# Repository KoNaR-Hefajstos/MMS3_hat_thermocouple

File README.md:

Dokumentacja Hat'a: Moduł wejść termopar

## Sekcja 1: Dokumentacja Hat'a

### Krótki opis projektu
Hat thermoucople umożliwia wykonywanie pomiarów temperatury przy użyciu termopar. 
Płytka jest wyposażona w 8 wejść oraz przetwornik analogowy cyfrowy, dedykowany do obsługi termopar typu K ze zintegrowaną kompensacją zimnego końca

### Zgodność ze standardem ChainBus

* ✅  Używa złącza ChainBus, nie zmienia jego miejsca ani pinoutu.
* ✅  Używa wyłącznie interfejsów I2C, SPI lub UART i nie inicjuje samodzielnie nowych transmisji (Nie jest master'em I2C albo SPI).
* ✅  Spełnia wymagania mechaniczne standardu (wymiary PCB, rozstaw otworów).
* ✅  Pobiera maksymalny prąd zgodny z ilością na jednego hat'a
* ✅  Obsługuje napięcie wejściowe BRD_VIN do wartości 48V.

### Komunikacja i adresowanie
Układ komunikuje się za pomocą jednokierunkowego interfejsu SPI w trybie tylko do odczytu. 
To które wyjście jest aktualnie odczytywane zależy od stanu pinu CS układu scalonego MAX31855KASA+T, do ustalaniu stanu tych pinów zastosowany został I2C multipexer

| Układ (IC)                | Funkcja         |  Address   |
| :------------             | :-------------- | :--------: |
| **TCA9535PWR_C130204**    | I2C multiplexer | `0000000b` |

#### Magistrala SPI
Urządzenia SPI podłączone są bezpośrednio do magistrali systemowej bez użycia dodatkowych multiplekserów.

| Układ (IC)         | Funkcja                     | chainbus/multiplexer |
| :----------        | :-------------------------- | :------------------: |
| **MAX31855KASA+T** | Sterownik silnika krokowego |      `chainbus`      |

### Pinout złączy

| Jn       | Co              | Jaki pin co robi                                                       |
| :-----   | :---------------| :----------------------------------------------------------------------|
| **TH00** | Termopara 1     | Pin 1 Ujemne wejście Termopary<br> Pin 2 Dodatnie wejście Termopary<br>|
| **TH01** | Termopara 2     | Pin 1 Ujemne wejście Termopary<br> Pin 2 Dodatnie wejście Termopary<br>|
| **TH02** | Termopara 3     | Pin 1 Ujemne wejście Termopary<br> Pin 2 Dodatnie wejście Termopary<br>|
| **TH03** | Termopara 4     | Pin 1 Ujemne wejście Termopary<br> Pin 2 Dodatnie wejście Termopary<br>|
| **TH04** | Termopara 5     | Pin 1 Ujemne wejście Termopary<br> Pin 2 Dodatnie wejście Termopary<br>|
| **TH05** | Termopara 6     | Pin 1 Ujemne wejście Termopary<br> Pin 2 Dodatnie wejście Termopary<br>|
| **TH06** | Termopara 7     | Pin 1 Ujemne wejście Termopary<br> Pin 2 Dodatnie wejście Termopary<br>|
| **TH07** | Termopara 8     | Pin 1 Ujemne wejście Termopary<br> Pin 2 Dodatnie wejście Termopary<br>|

### Typ możliwych termopar 
Termopary typu K, J, N, T, S, R lub E. Przetwornik umożliwia rozdzielczość temperatury do 0,25°C, pozwala na odczyty do +1800°C i tak niskie jak -270°C, a dokładność termopary wynosi ±2°C dla temperatur od -200°C do +700°C w przypadku termopar typu K.

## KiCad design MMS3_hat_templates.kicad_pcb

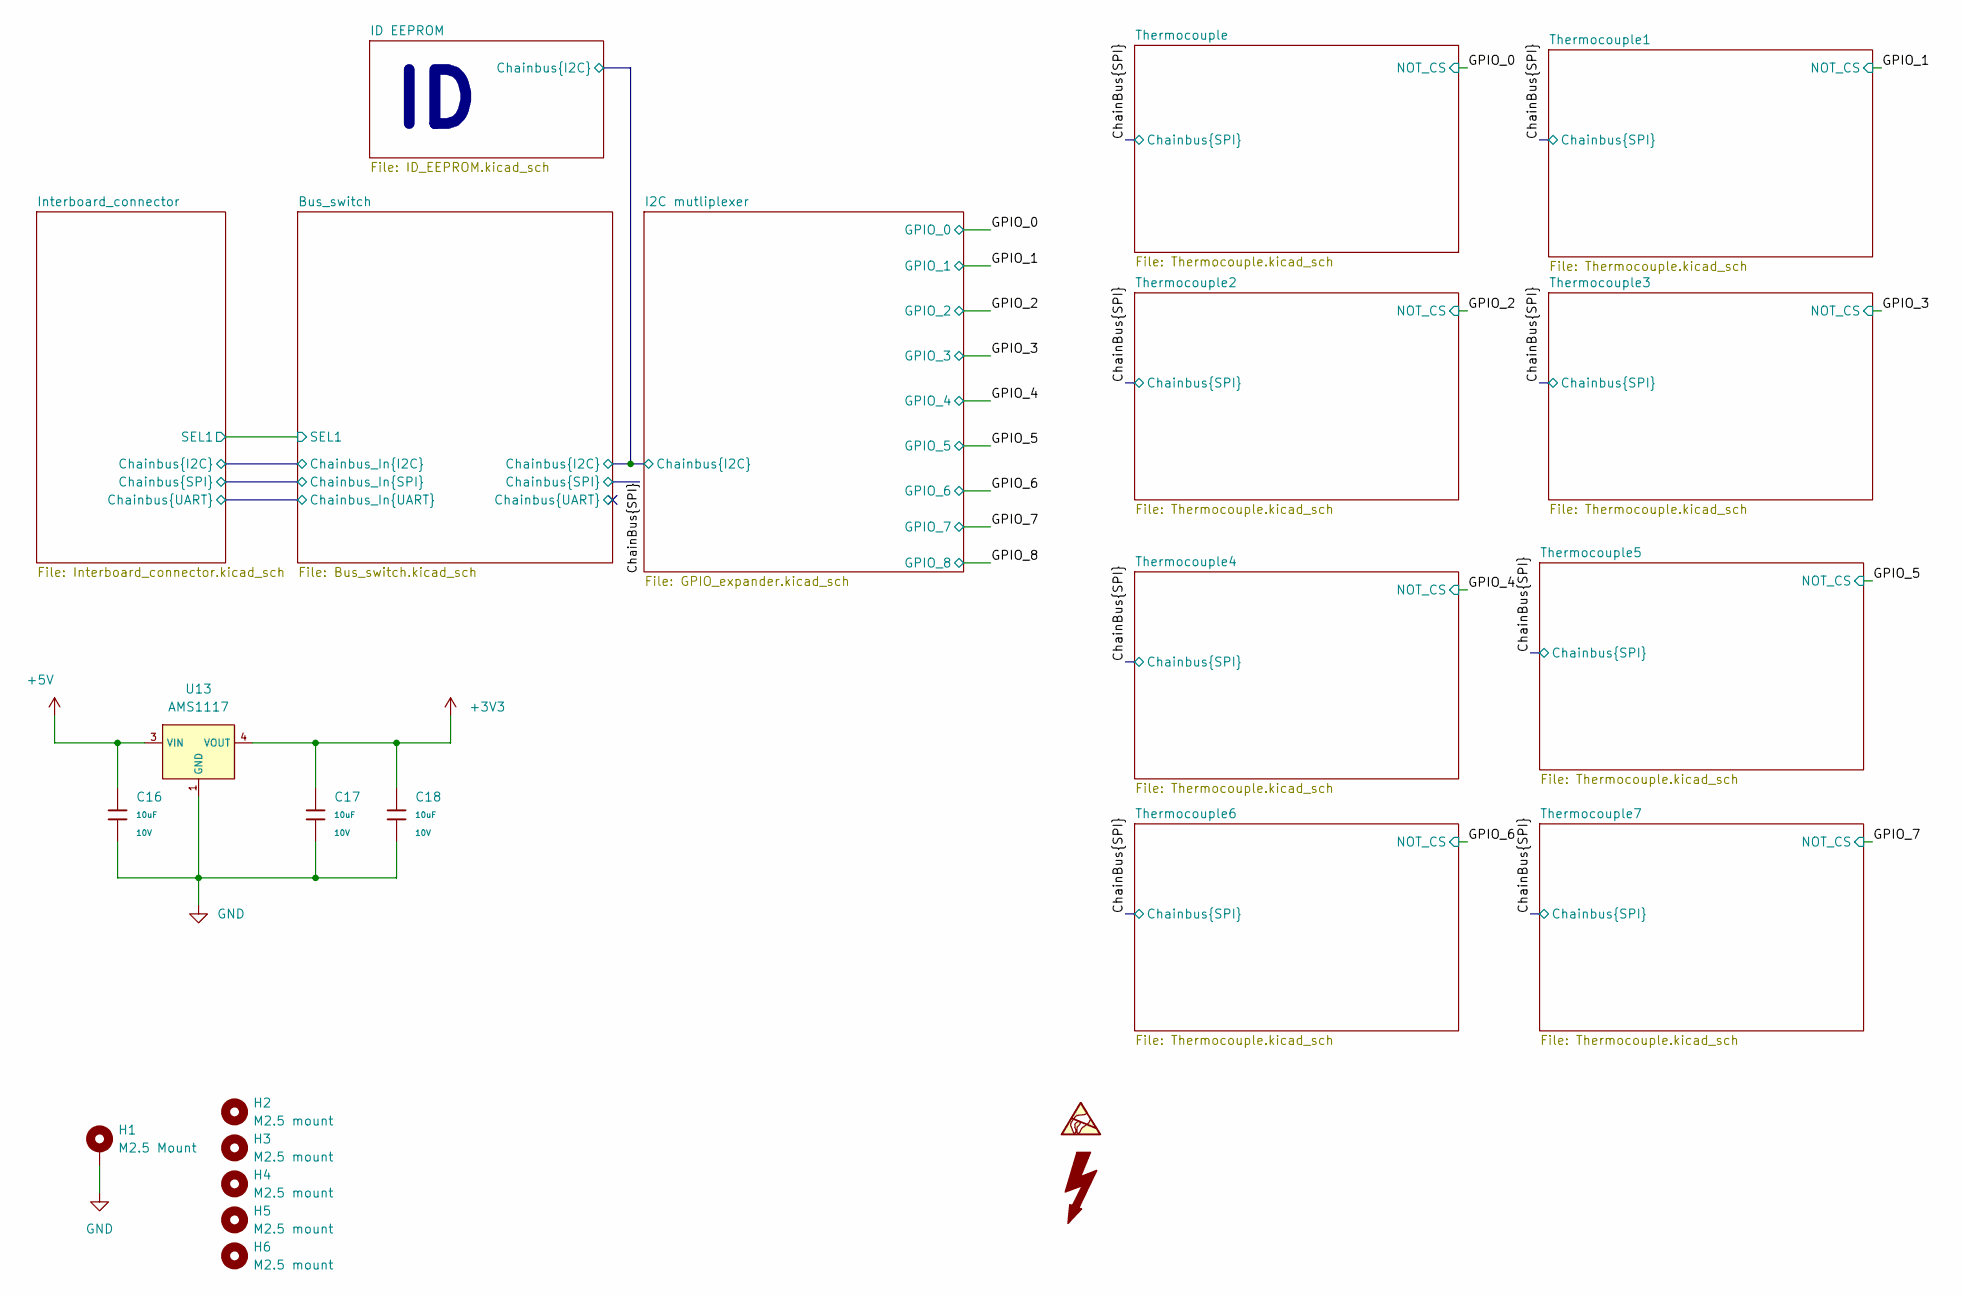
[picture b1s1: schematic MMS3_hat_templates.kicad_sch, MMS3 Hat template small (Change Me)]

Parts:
C16, C17, C18: 10uF; C_0603; Voltage Rated 10V; Tolerance ±10%; Part CL10A106KP8NNNC; LCSC C19702
H1: M2.5 Mount; MountingHole_2.7mm_M2.5_DIN965_Pad_TopOnly
H2, H3, H4, H5, H6: M2.5 mount; MountingHole_2.7mm_M2.5
U13: AMS1117; SOT-223-3_L6.5-W3.4-P2.30-LS7.0-BR; Output Voltage 3.3V; Dropout Voltage 1.3V@(800mA); Part AMS1117-3.3; LCSC C6186

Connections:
+3V3: C17.1, C18.1, U13.2 (VOUT), U13.4 (VOUT); also elsewhere on the board
+5V: C16.1, U13.3 (VIN); also elsewhere on the board
GND: C16.2, C17.2, C18.2, H1.1 (1_1), U13.1 (GND); also elsewhere on the board

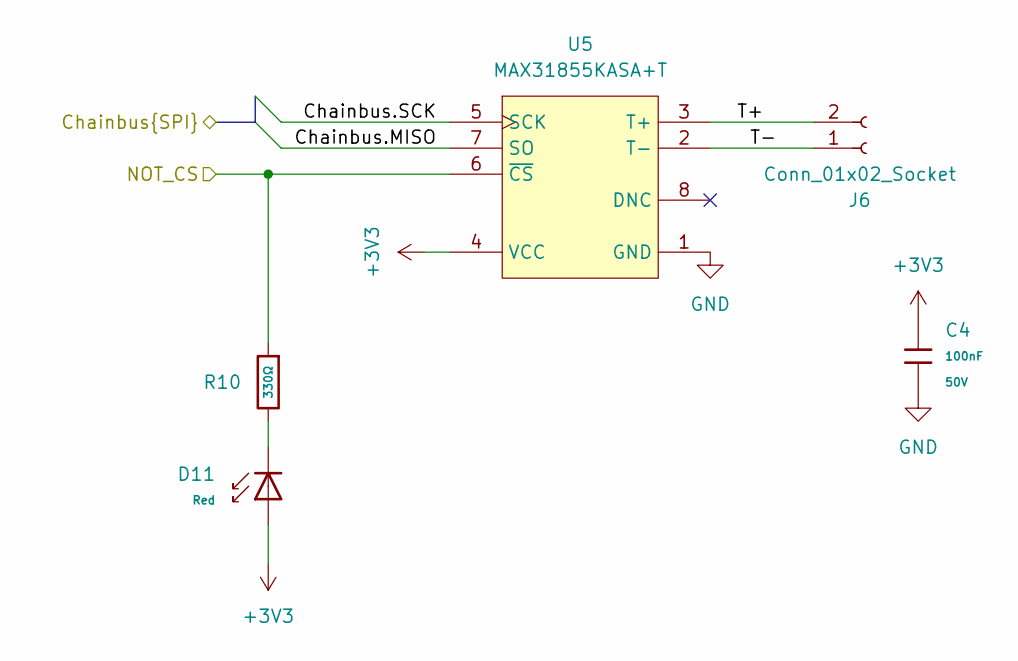
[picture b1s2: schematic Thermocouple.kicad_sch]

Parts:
C4: 100nF; C_0603; Voltage Rated 50V; Tolerance ±10%; Part CC0603KRX7R9BB104; LCSC C14663
D11: Red; D_0603; Part KT-0603R; LCSC C2286
J6: Conn_01x02_Socket; JST_XH_S2B-XH-A_1x02_P2.50mm_Horizontal
R10: 330Ω; R_0402; Overload Voltage (Max) 50V; Tolerance ±1%; Part 0402WGF3300TCE; LCSC C25104
U5: MAX31855KASA+T; SO-8_L4.9-W3.9-P1.27-LS5.9-BL; MPN MAX31855KASA+T; LCSC Part C52028

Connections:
+3V3: C4.1, D11.2, U5.4 (VCC); also elsewhere on the board
/ChainBus.MISO: U5.7 (SO); also elsewhere on the board
/ChainBus.SCK: U5.5 (SCK); also elsewhere on the board
/GPIO_1: R10.1, U5.6 (~CS); also elsewhere on the board
/Thermocouple1/T+: J6.2, U5.3 (T+)
/Thermocouple1/T-: J6.1, U5.2 (T-)
GND: C4.2, U5.1 (GND); also elsewhere on the board
unnamed: D11.1, R10.2

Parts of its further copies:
C5, C6, C7, C8, C9, C10, C11: 100nF; C_0603; Voltage Rated 50V; Tolerance ±10%; Part CC0603KRX7R9BB104; LCSC C14663
D12, D13, D14, D15, D16, D17, D18: Red; D_0603; Part KT-0603R; LCSC C2286
J7, J8, J9, J10, J11, J12, J13: Conn_01x02_Socket; JST_XH_S2B-XH-A_1x02_P2.50mm_Horizontal
R11, R12, R13, R14, R15, R16, R17: 330Ω; R_0402; Overload Voltage (Max) 50V; Tolerance ±1%; Part 0402WGF3300TCE; LCSC C25104
U16, U17, U18, U19, U20, U21, U22: MAX31855KASA+T; SO-8_L4.9-W3.9-P1.27-LS5.9-BL; MPN MAX31855KASA+T; LCSC Part C52028

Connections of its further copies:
+3V3: C5.1, C6.1, C7.1, C8.1, C9.1, C10.1, C11.1, D12.2, D13.2, D14.2, D15.2, D16.2, D17.2, D18.2, U16.4 (VCC), U17.4 (VCC), U18.4 (VCC), U19.4 (VCC), U20.4 (VCC), U21.4 (VCC), U22.4 (VCC); also elsewhere on the board
/ChainBus.MISO: U16.7 (SO), U17.7 (SO), U18.7 (SO), U19.7 (SO), U20.7 (SO), U21.7 (SO), U22.7 (SO); also elsewhere on the board
/ChainBus.SCK: U16.5 (SCK), U17.5 (SCK), U18.5 (SCK), U19.5 (SCK), U20.5 (SCK), U21.5 (SCK), U22.5 (SCK); also elsewhere on the board
/GPIO_0: R11.1, U16.6 (~CS); also elsewhere on the board
/GPIO_2: R12.1, U17.6 (~CS); also elsewhere on the board
/GPIO_3: R13.1, U18.6 (~CS); also elsewhere on the board
/GPIO_4: R14.1, U19.6 (~CS); also elsewhere on the board
/GPIO_5: R15.1, U20.6 (~CS); also elsewhere on the board
/GPIO_6: R16.1, U21.6 (~CS); also elsewhere on the board
/GPIO_7: R17.1, U22.6 (~CS); also elsewhere on the board
/Thermocouple2/T+: J8.2, U17.3 (T+)
/Thermocouple2/T-: J8.1, U17.2 (T-)
/Thermocouple3/T+: J9.2, U18.3 (T+)
/Thermocouple3/T-: J9.1, U18.2 (T-)
/Thermocouple4/T+: J10.2, U19.3 (T+)
/Thermocouple4/T-: J10.1, U19.2 (T-)
/Thermocouple5/T+: J11.2, U20.3 (T+)
/Thermocouple5/T-: J11.1, U20.2 (T-)
/Thermocouple6/T+: J12.2, U21.3 (T+)
/Thermocouple6/T-: J12.1, U21.2 (T-)
/Thermocouple7/T+: J13.2, U22.3 (T+)
/Thermocouple7/T-: J13.1, U22.2 (T-)
/Thermocouple/T+: J7.2, U16.3 (T+)
/Thermocouple/T-: J7.1, U16.2 (T-)
GND: C5.2, C6.2, C7.2, C8.2, C9.2, C10.2, C11.2, U16.1 (GND), U17.1 (GND), U18.1 (GND), U19.1 (GND), U20.1 (GND), U21.1 (GND), U22.1 (GND); also elsewhere on the board
unnamed: D12.1, R11.2
unnamed: D13.1, R12.2
unnamed: D14.1, R13.2
unnamed: D15.1, R14.2
unnamed: D16.1, R15.2
unnamed: D17.1, R16.2
unnamed: D18.1, R17.2

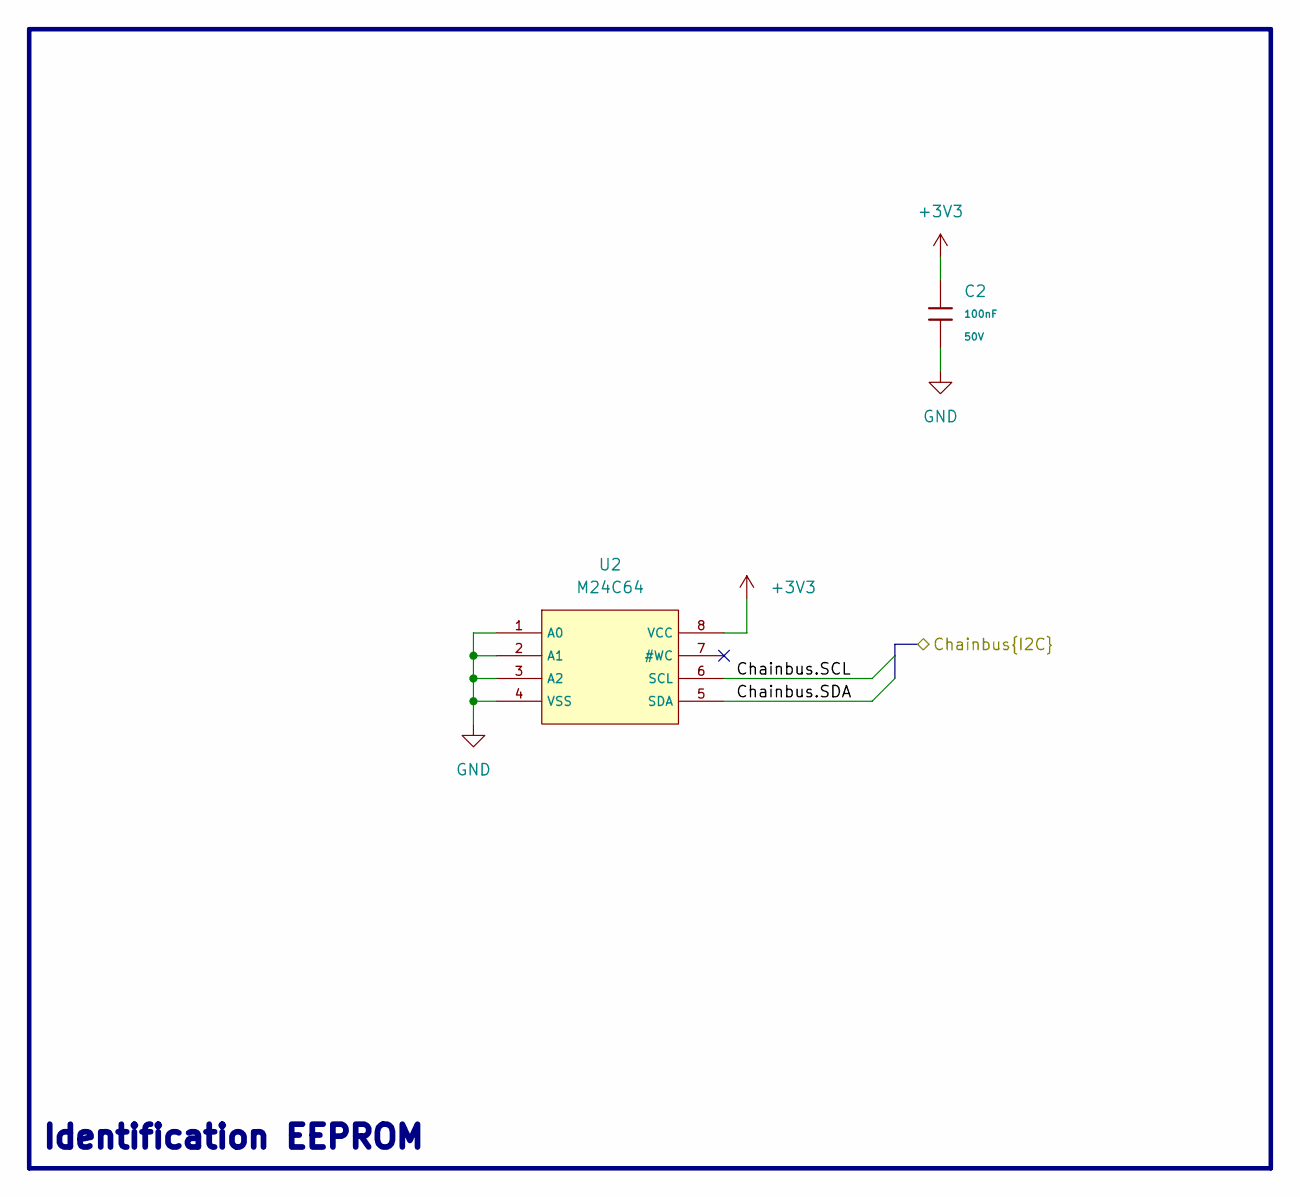
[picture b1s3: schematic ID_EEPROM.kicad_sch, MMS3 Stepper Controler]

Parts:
C2: 100nF; C_0603; Voltage Rated 50V; Tolerance ±10%; Part CC0603KRX7R9BB104; LCSC C14663
U2: M24C64; SOIC-8_L5.0-W4.0-P1.27-LS6.0-BL; Supply Voltage 1.8V~5.5V; Part M24C64-RMN6TP; LCSC C79988

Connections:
+3V3: C2.1, U2.8 (VCC); also elsewhere on the board
/Bus_switch/Chainbus.SCL: U2.6 (SCL); also elsewhere on the board
/Bus_switch/Chainbus.SDA: U2.5 (SDA); also elsewhere on the board
GND: C2.2, U2.1 (A0), U2.2 (A1), U2.3 (A2), U2.4 (VSS); also elsewhere on the board

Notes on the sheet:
Identification EEPROM

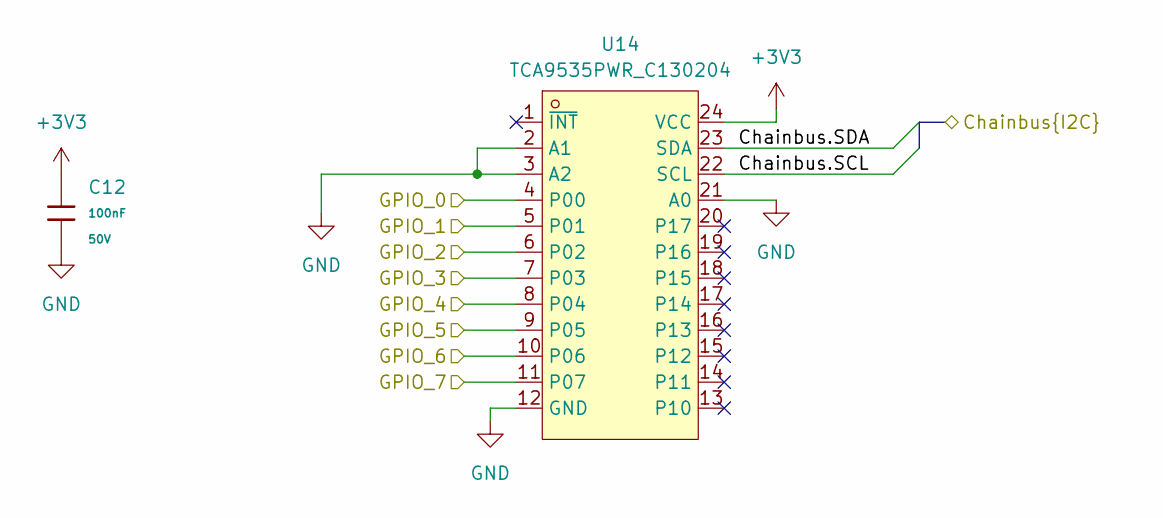
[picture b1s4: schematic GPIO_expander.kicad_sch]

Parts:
C12: 100nF; C_0603; Voltage Rated 50V; Tolerance ±10%; Part CC0603KRX7R9BB104; LCSC C14663
U14: TCA9535PWR_C130204; TSSOP-24_L7.8-W4.4-P0.65-LS6.4-BL; MPN TCA9535PWR; LCSC Part C130204

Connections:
+3V3: C12.1, U14.24 (VCC); also elsewhere on the board
/Bus_switch/Chainbus.SCL: U14.22 (SCL); also elsewhere on the board
/Bus_switch/Chainbus.SDA: U14.23 (SDA); also elsewhere on the board
/GPIO_0: U14.4 (P00); also elsewhere on the board
/GPIO_1: U14.5 (P01); also elsewhere on the board
/GPIO_2: U14.6 (P02); also elsewhere on the board
/GPIO_3: U14.7 (P03); also elsewhere on the board
/GPIO_4: U14.8 (P04); also elsewhere on the board
/GPIO_5: U14.9 (P05); also elsewhere on the board
/GPIO_6: U14.10 (P06); also elsewhere on the board
/GPIO_7: U14.11 (P07); also elsewhere on the board
GND: C12.2, U14.2 (A1), U14.3 (A2), U14.12 (GND), U14.21 (A0); also elsewhere on the board

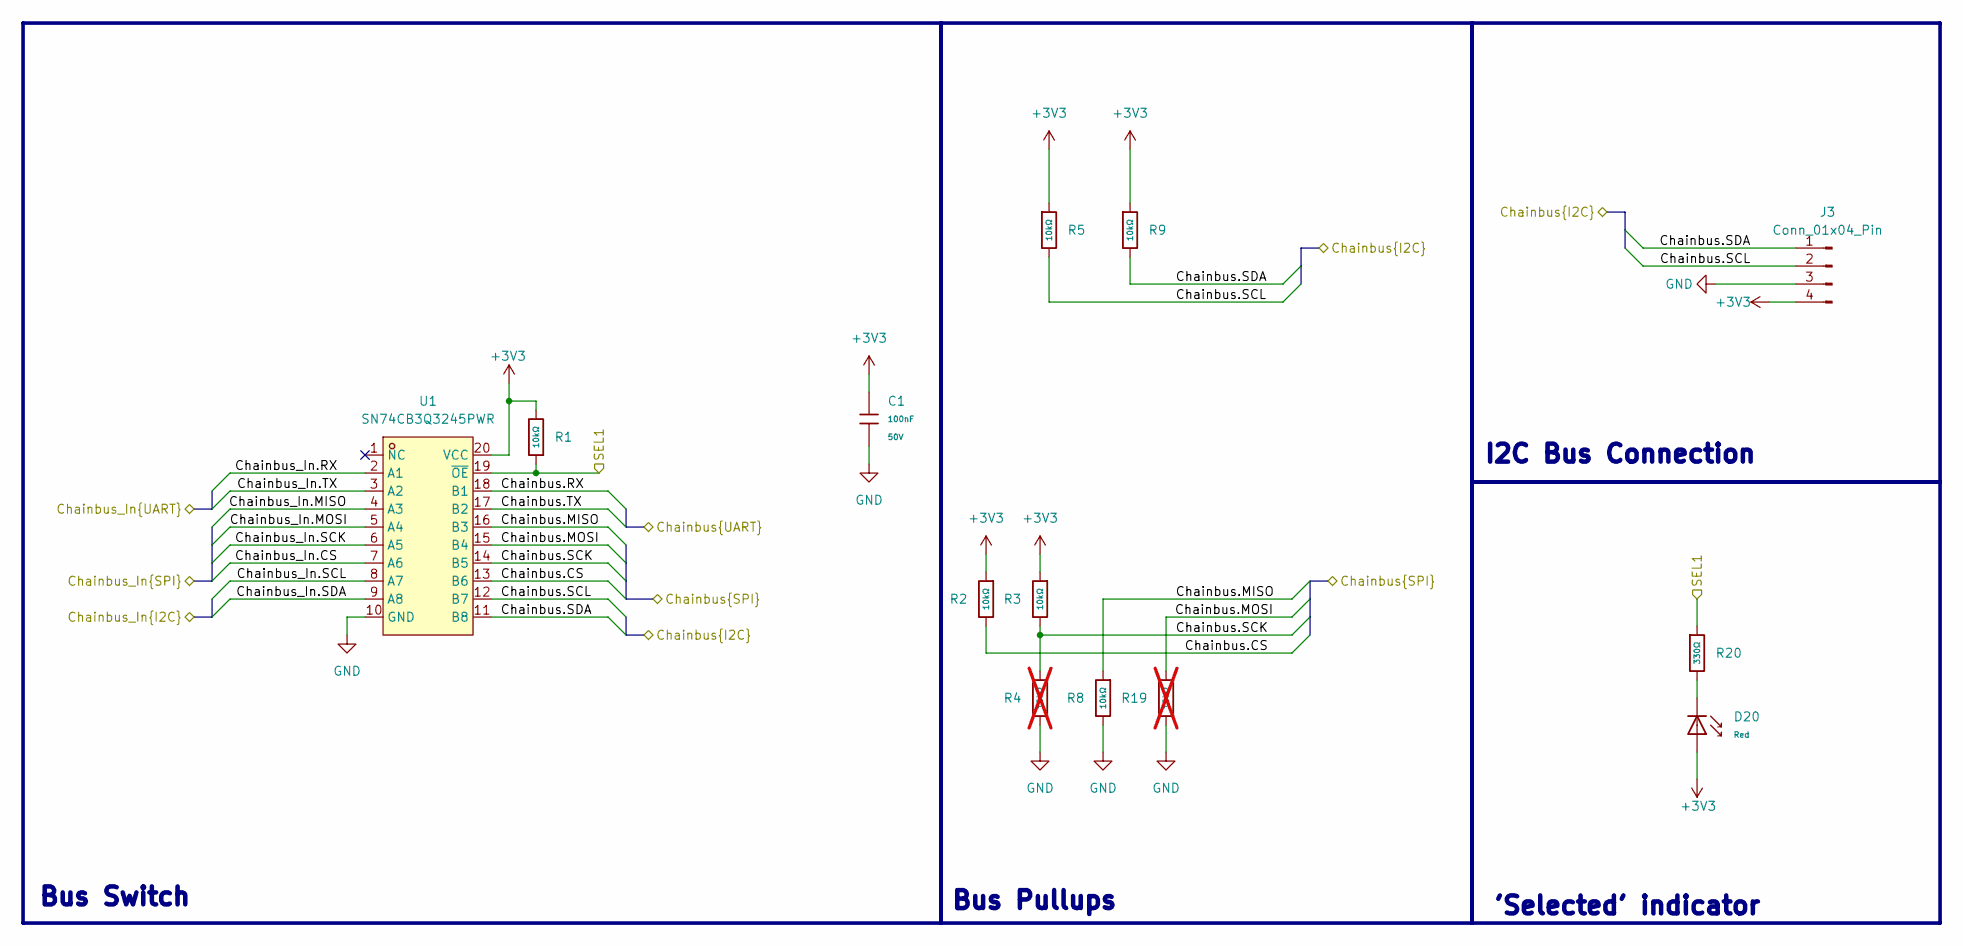
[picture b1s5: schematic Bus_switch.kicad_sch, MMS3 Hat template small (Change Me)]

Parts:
C1: 100nF; C_0603; Voltage Rated 50V; Tolerance ±10%; Part CC0603KRX7R9BB104; LCSC C14663
D20: Red; D_0603; Part KT-0603R; LCSC C2286
J3: Conn_01x04_Pin; PinHeader_1x04_P2.54mm_Vertical
R1, R2, R3, R5, R8, R9: 10kΩ; R_0402; Overload Voltage (Max) 50V; Tolerance ±1%; Part 0402WGF1002TCE; LCSC C25744
R4, R19: 10kΩ; R_0402; Overload Voltage (Max) 50V; Tolerance ±1%; Part 0402WGF1002TCE; LCSC C25744; not fitted
R20: 330Ω; R_0402; Overload Voltage (Max) 50V; Tolerance ±1%; Part 0402WGF3300TCE; LCSC C25104
U1: SN74CB3Q3245PWR; TSSOP-20_L6.5-W4.4-P0.65-LS6.4-BL; MPN SN74CB3Q3245PWR; LCSC Part C470961

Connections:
+3V3: C1.1, D20.2, J3.4, R1.2, R2.1, R3.1, R5.1, R9.1, U1.20 (VCC); also elsewhere on the board
/Bus_switch/Chainbus.RX: U1.18 (B1)
/Bus_switch/Chainbus.SCL: J3.2, R5.2, U1.12 (B7); also elsewhere on the board
/Bus_switch/Chainbus.SDA: J3.1, R9.2, U1.11 (B8); also elsewhere on the board
/Bus_switch/Chainbus.TX: U1.17 (B2)
/Bus_switch/Chainbus_In.CS: U1.7 (A6); also elsewhere on the board
/Bus_switch/Chainbus_In.MISO: U1.4 (A3); also elsewhere on the board
/Bus_switch/Chainbus_In.MOSI: U1.5 (A4); also elsewhere on the board
/Bus_switch/Chainbus_In.RX: U1.2 (A1); also elsewhere on the board
/Bus_switch/Chainbus_In.SCK: U1.6 (A5); also elsewhere on the board
/Bus_switch/Chainbus_In.SCL: U1.8 (A7); also elsewhere on the board
/Bus_switch/Chainbus_In.SDA: U1.9 (A8); also elsewhere on the board
/Bus_switch/Chainbus_In.TX: U1.3 (A2); also elsewhere on the board
/Bus_switch/SEL1: R1.1, R20.1, U1.19 (~OE); also elsewhere on the board
/ChainBus.CS: R2.2, U1.13 (B6)
/ChainBus.MISO: R8.1, U1.16 (B3); also elsewhere on the board
/ChainBus.MOSI: R19.1, U1.15 (B4)
/ChainBus.SCK: R3.2, R4.1, U1.14 (B5); also elsewhere on the board
GND: C1.2, J3.3, R4.2, R8.2, R19.2, U1.10 (GND); also elsewhere on the board
unnamed: D20.1, R20.2

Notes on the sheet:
Bus Switch
Bus Pullups
'Selected' indicator
I2C Bus Connection

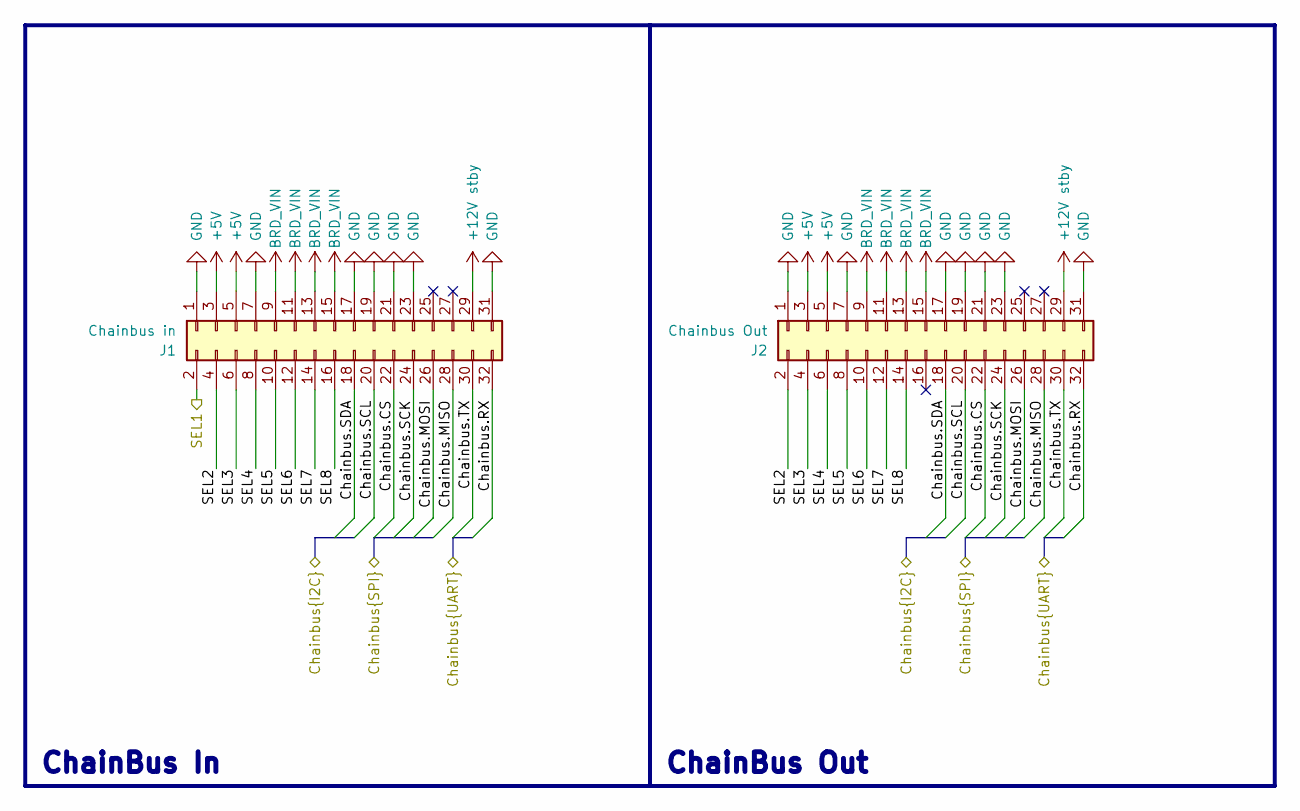
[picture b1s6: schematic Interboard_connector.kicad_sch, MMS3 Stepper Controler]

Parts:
J1: Chainbus in; PinHeader_2x16_P2.54mm_Vertical_SMD
J2: Chainbus Out; PinSocket_2x16_P2.54mm_Vertical_SMD

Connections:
+5V: J1.3, J1.5, J2.3, J2.5; also elsewhere on the board
+12V stby: J1.29, J2.29
/Bus_switch/Chainbus_In.CS: J1.22, J2.22; also elsewhere on the board
/Bus_switch/Chainbus_In.MISO: J1.28, J2.28; also elsewhere on the board
/Bus_switch/Chainbus_In.MOSI: J1.26, J2.26; also elsewhere on the board
/Bus_switch/Chainbus_In.RX: J1.32, J2.32; also elsewhere on the board
/Bus_switch/Chainbus_In.SCK: J1.24, J2.24; also elsewhere on the board
/Bus_switch/Chainbus_In.SCL: J1.20, J2.20; also elsewhere on the board
/Bus_switch/Chainbus_In.SDA: J1.18, J2.18; also elsewhere on the board
/Bus_switch/Chainbus_In.TX: J1.30, J2.30; also elsewhere on the board
/Bus_switch/SEL1: J1.2; also elsewhere on the board
/Interboard_connector/SEL2: J1.4, J2.2
/Interboard_connector/SEL3: J1.6, J2.4
/Interboard_connector/SEL4: J1.8, J2.6
/Interboard_connector/SEL5: J1.10, J2.8
/Interboard_connector/SEL6: J1.12, J2.10
/Interboard_connector/SEL7: J1.14, J2.12
/Interboard_connector/SEL8: J1.16, J2.14
BRD_VIN: J1.9, J1.11, J1.13, J1.15, J2.9, J2.11, J2.13, J2.15
GND: J1.1, J1.7, J1.17, J1.19, J1.21, J1.23, J1.31, J2.1, J2.7, J2.17, J2.19, J2.21, J2.23, J2.31; also elsewhere on the board

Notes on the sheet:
ChainBus In
ChainBus Out

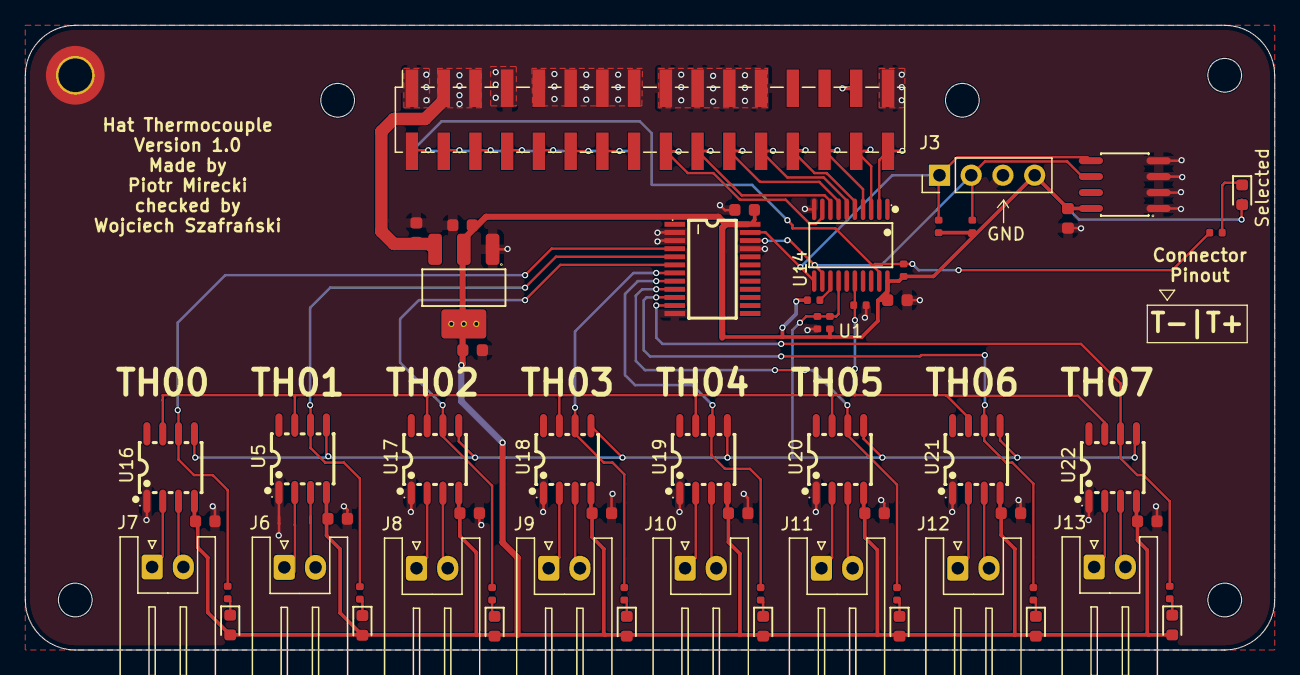
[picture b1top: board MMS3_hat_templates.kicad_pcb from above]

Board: 2 copper layers, 100.0 x 50.0 mm, 68 parts (1 on the bottom side), 59 nets.

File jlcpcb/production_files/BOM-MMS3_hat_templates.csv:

Comment,Designator,Footprint,LCSC,Quantity
100nF,"C1,C10,C11,C12,C2,C4,C5,C6,C7,C8,C9",C_0603,C14663,11
10kΩ,"R1,R2,R3,R5,R8,R9",R_0402,C25744,6
10uF,"C16,C17,C18",C_0603,C19702,3
330Ω,"R10,R11,R12,R13,R14,R15,R16,R17,R20",R_0402,C25104,9
AMS1117,U13,SOT-223-3_L6.5-W3.4-P2.30-LS7.0-BR,C6186,1
M24C64,U2,SOIC-8_L5.0-W4.0-P1.27-LS6.0-BL,C79988,1
MAX31855KASA+T,"U16,U17,U18,U19,U20,U21,U22,U5",SO-8_L4.9-W3.9-P1.27-LS5.9-BL,C52028,8
Red,"D11,D12,D13,D14,D15,D16,D17,D18,D20",D_0603,C2286,9
SN74CB3Q3245PWR,U1,TSSOP-20_L6.5-W4.4-P0.65-LS6.4-BL,C470961,1
TCA9535PWR_C130204,U14,TSSOP-24_L7.8-W4.4-P0.65-LS6.4-BL,C130204,1

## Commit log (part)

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2026-02-26 template board cleansed
2026-02-26 first steps
    thermocouple and GPIO expander sheets done
2026-02-27 done ( v 1.0 - check required )
2026-04-18 fixed selected led polarity
2026-04-20 generated final gerber
2026-06-24 updated silkscreen
